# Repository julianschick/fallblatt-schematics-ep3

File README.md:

# Fallblattanzeiger der Deutschen Bahn

Die Deutsche Bahn verwendete lange Zeit standardisierte Fallblattanzeigemodule mit Platinen, die mit *MANTronic* beschriftet sind, also vermutlich von der Firma MAN hergestellt wurden.

Möchte man diese alten Module wieder zum klappern bringen, so hat man grundsätzlich erstmal zwei Möglichkeiten. Die Module wurden offenbar über eine RS485-Schnittstelle angesteuert. Das Protokoll ist vermutlich ein Protokoll ähnlich dem CAN-Bus. Meine gründliche Recherche ergab allerdings keine Quellen im Internet, denen bekannt ist, wie dieses Protokoll genau aussieht. Diese Möglichkeit ist daher eher schwierig.

Eine andere Möglichkeit besteht darin, den zentralen ZiLOG-Microcontroller auf der Platine durch einen eigenen Microcontroller zu ersetzen. Ich habe zu diesem Zweck den ZiLOG-Chip von der Platine geschnitten. Praktischerweise sind auf der Platine nicht nur die SMD-Lötpads für den ZiLOG-Chip, sondern auch etwas größere Pads im DIP-Raster, an die man sehr gut Kabel anlöten kann. Vermutlich ein überbleibsel von älteren Platinenversionen, bei denen ein größerer Microcontroller verwendet wurde.

Mit einer Kombination aus eigener Intuition und Bestätigung durch die Schaltpläne dieses [Hackaday-Projekts](https://hackaday.io/project/9070-fallblattfahrzielanzeige-of-s-bahn-berlin) war es nicht schwer, die Pinbelegung des ZiLOG-Controllers zu ermitteln und so herauszufinden, welche Pins angesteuert bzw. ausgelesen werden müssen. Weiter unten habe ich das mit einer Skizze und einem Foto dokumentiert.

Gemäß der Einteilung im [Wikipedia-Artikel](https://de.wikipedia.org/wiki/Fallblattanzeige) in die vom Aufbau her zu unterscheidenden Epochen 1 bis 4 fällt diese Anzeige in die Epoche 3.

## Funktionsweise

Die Funktionsweise des Fallblattmoduls ist gar nicht so kompliziert. Die Blätter sitzen auf einer Welle die über ein Getriebe von einem Synchronmotor (Berger Lahr RSM 42/12 NG) angetrieben wird, der tatsächlich auch heute noch erhältlich ist ([Datenblatt](https://www.abi.nl/assets/uploads/Downloads/Aandrijvingen/Kleine%20vertragingsmotoren/Synchroonmotoren/Catalogus_RSM_D.pdf)).
Damit der Motor weiß, wann er anhalten soll, sind zwei Infrarot-Transmitter mit Photodioden als Sensoren verbaut. Ein Sensor erzeugt pro fallendem Blatt einen erhöhten Spannungspegel, der andere dient zur Erkennung der Nullposition und weist nur einmal pro Umdrehung der ganzen Welle einen erhöhten Spannungspegel auf. Das ganze wird durch weiße Blenden bewerkstelligt, die beim Vorbeistreichen am Sensor durch die Reflektion der Infrarotstrahlen des Transmitters für mehr Einfall von Infrarotstrahlung in die Photodiode und dadurch einen höheren Spannungspegel sorgen.

Die Verdrahtung der Sensoren auf der Platine ist etwas eigenwillig. Beide Sensoren gehen auf den gleichen Eingang (Sensor IN), an dem mit Hilfe eines ADC die anliegende Spannung messen kann. Um die Sensoren einzeln abfragen zu können, kann man die Sensoren getrennt mit Spannung versorgen (Sensor 1 / Sensor 2) und dann jeweils nur den Sensor auslesen, der mit Spannung versorgt wird. Der Motor ist einfach anzusteuern: Zieht man den Motor-Pin auf LOW, läuft der Motor los, zieht man ihn auf HIGH (3,3V oder 5V), bleibt der Motor stehen.

## Pinbelegung ZiLOG

## Stromversorgung

Die Platine hat zwei Stromkreise, ein Niederspannungsstromkreis für die Steuerungselektronik, der ursprünglich wohl mit 5 V DC betrieben wurde. Ich habe auch mit nur 3.3 V DC keine Probleme festgestellt. Der andere Stromkreis sollte mit etwa 42 V AC bei 50 Hz gespeist werden. Mit diesem Strom wird der Synchronmotor zum Antrieb der Welle betrieben. Die folgende Skizze zeigt die Pinbelegung des Wannensteckers am Rand der Platine bezüglich der Spannungsversorgung.

## Code

Code für die Platine kann in den Repositories [fallblatt-code-legacy](https://github.com/julianschick/fallblatt-code-legacy) und [fallblatt-code](https://github.com/julianschick/fallblatt-code) gefunden werden, wobei letzterer aktueller und mit mehr Funktionen ausgestattet ist.

## Teileliste

Mit passenden Artikelbezeichnungen für den Berliner Elektroteilehändler [Segor](https://www.segor.de).

Anzahl | Beschreibung | Segor-Artikelbezeichnung | Alt. Link
--|--|--|--
1 | Schraubklemme 2-polig RM 7,5mm | *ARK 2-Lift/RM7,5*
1 | Varistor >300V RM 7,5mm | *VDR 300-K 7* | [Reichelt](https://www.reichelt.de/varistor-rm-7-5-mm-300-v-10-epc-b72210-s030-p239932.html)
1 | Brückengleichrichter Rund, Wechselstrompins gegenüber, RM 5mm | *B 80C1500 R* | [Reichelt](https://www.reichelt.de/brueckengleichrichter-100-v-1-5-a-b70c1500rund-p181713.html)
1 | Transformator 9V _Block VB 2,0/1/9_ | | [Reichelt](https://www.reichelt.de/printtrafo-2-va-9-v-222-ma-rm-20-mm-ei-30-15-5-109-p27328.html)
1 | Transformator 2x24V *Block VC 10/2/24* | | [Reichelt](https://www.reichelt.de/printtrafo-10-va-2x-24-v-2x-208-ma-rm-27-5-mm-ei-48-16-8-224-p27492.html)
1 | ESP32-Development-Board (es gibt 2 Varianten bei eBay, für diese Platine wird die unüblichere mit 19 Pins je Reihe und GND/VCC auf gegenüberliegenden, nicht nebeneinanderliegenden Pins benötigt; diese wird oft unter dem Namen _ESP32S_ verkauft.) |
1 | Spannungsregler 3,3V Formfaktor TO-220 _STM LD1117 V33C_ | *LD 1117 V33* | [Reichelt](https://www.reichelt.de/ldo-regler-fest-3-3-v-to-220-ld1117-v33c-p200891.html)
1 | Elektrolytkondensator 470u, >12V, RM 5mm | *ELRA 470u-25/105°lowESR* |
1 | Elektrolytkondensator 10u, >12V, RM 2mm | *ELRA 470u-35/105°* |
1 | Kondensator 100n, >12V, RM 2,5mm | *u10-R2.5-X7R* |
1 | D-Sub Buchse 9-polig, Printmontage 90°, Abstand Pinreihe zu Steckerfläche 10mm | DS09F-90°-10mm |
1 | D-Sub Buchse 25-polig, Printmontage 90°, Abstand Pinreihe zu Steckerfläche 10mm | DS25F-90°-10mm |
4 | Pinheader 20-polig, Female, Vertikal, RM 2,54mm | 
2 | Pinheader 2-polig, Male, Vertikal, RM 2,54mm

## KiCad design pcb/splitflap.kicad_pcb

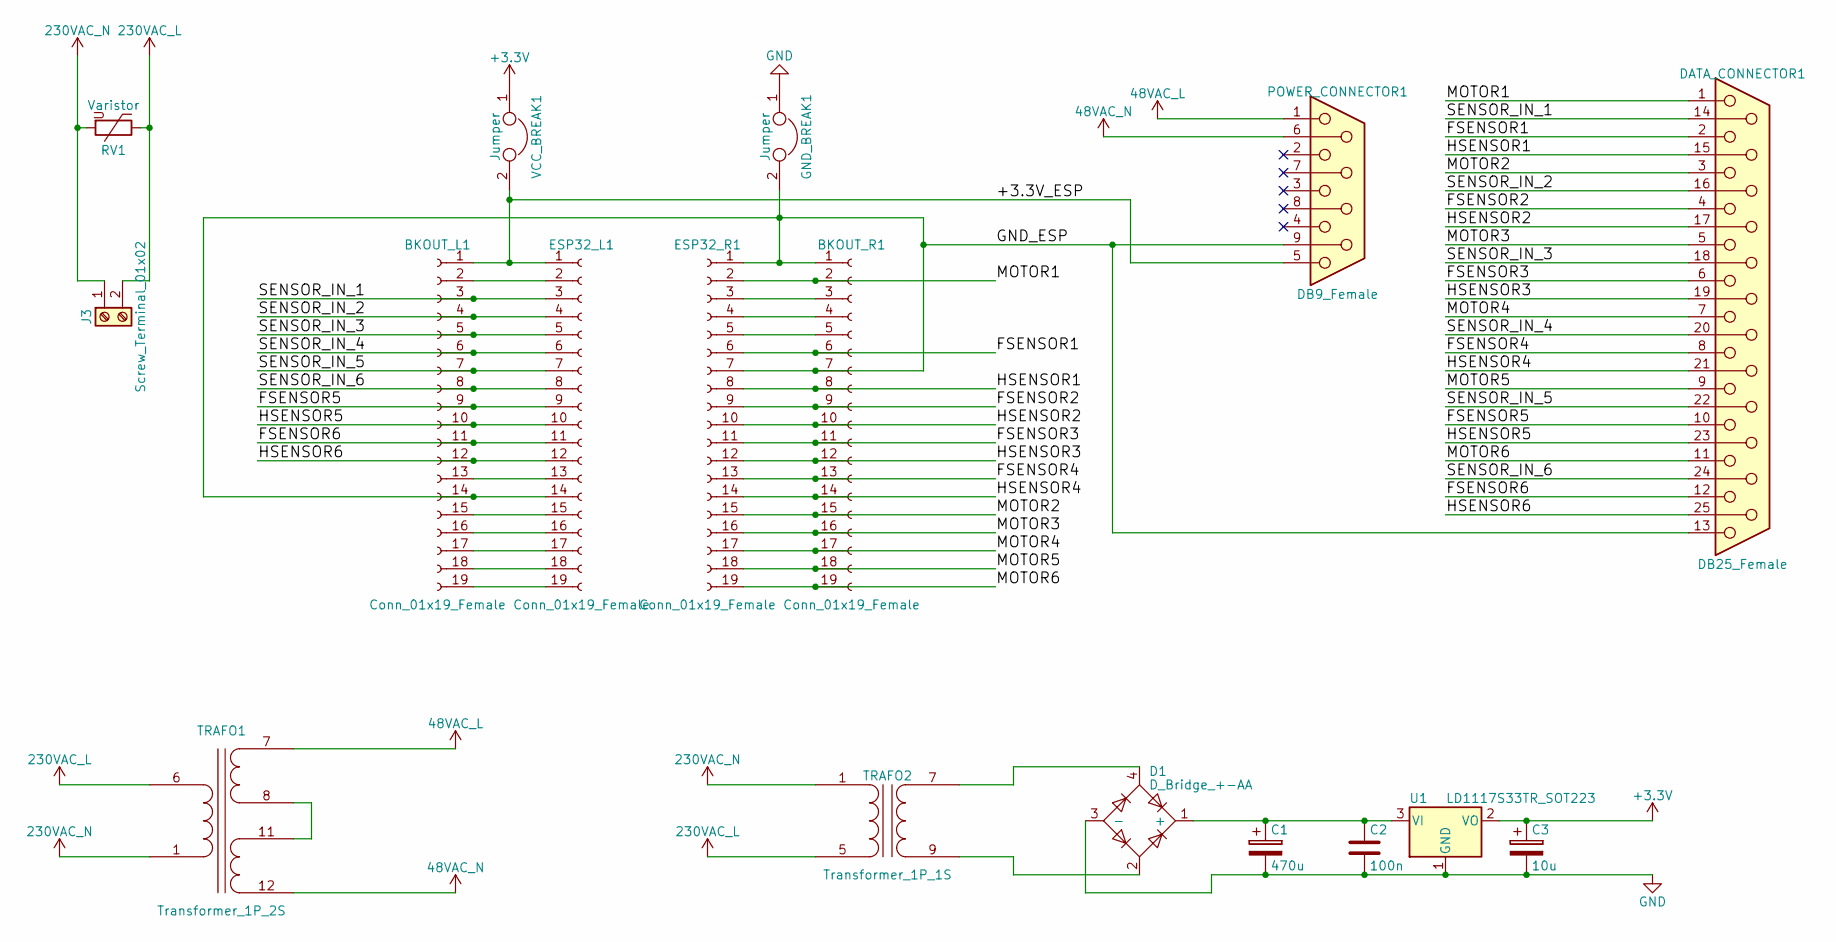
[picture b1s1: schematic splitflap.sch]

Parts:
BKOUT_L1: Conn_01x19_Female; Socket_Strip_Straight_1x20_Pitch2.54mm
BKOUT_R1: Conn_01x19_Female; Socket_Strip_Straight_1x20_Pitch2.54mm
C1: 470u; CP_Radial_D8.0mm_P5.00mm
C2: 100n; C_Rect_L4.0mm_W2.5mm_P2.50mm
C3: 10u; CP_Radial_D4.0mm_P2.00mm
D1: D_Bridge_+-AA; Diode_Bridge_Round_D8.9mm
DATA_CONNECTOR1: DB25_Female; DSUB-25_Female_Horizontal_Pitch2.77x2.54mm_EdgePinOffset9.4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
ESP32_L1, ESP32_R1: Conn_01x19_Female; Socket_Strip_Straight_1x20_Pitch2.54mm
GND_BREAK1: Jumper; Pin_Header_Straight_1x02_Pitch2.54mm
J3: Screw_Terminal_01x02; TerminalBlock_MetzConnect_Type171_RT13702HBWC_Pitch7.50mm
POWER_CONNECTOR1: DB9_Female; DSUB-9_Female_Horizontal_Pitch2.77x2.54mm_EdgePinOffset9.40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
RV1: Varistor; RV_Disc_D12_W3.9_P7.5
TRAFO1: Transformer_1P_2S; Transformer_CHK_EI48-10VA_2xSec_BLOCK
TRAFO2: Transformer_1P_1S; Transformer_CHK_EI30-2VA_1xSec
U1: LD1117S33TR_SOT223; TO-220-3_Vertical
VCC_BREAK1: Jumper; Pin_Header_Straight_1x02_Pitch2.54mm

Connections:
48VAC_L: POWER_CONNECTOR1.1, TRAFO1.7 (SA)
48VAC_N: POWER_CONNECTOR1.6, TRAFO1.12 (SD)
230VAC_L: J3.2, RV1.1, TRAFO1.6 (AA), TRAFO2.5 (AB)
230VAC_N: J3.1, RV1.2, TRAFO1.1 (AB), TRAFO2.1 (AA)
+3V3: C3.1, U1.2 (VO), VCC_BREAK1.1
/+3.3V_ESP: BKOUT_L1.1, ESP32_L1.1, POWER_CONNECTOR1.5, VCC_BREAK1.2
/FSENSOR1: BKOUT_R1.6, DATA_CONNECTOR1.2, ESP32_R1.6
/FSENSOR2: BKOUT_R1.9, DATA_CONNECTOR1.4, ESP32_R1.9
/FSENSOR3: BKOUT_R1.11, DATA_CONNECTOR1.6, ESP32_R1.11
/FSENSOR4: BKOUT_R1.13, DATA_CONNECTOR1.8, ESP32_R1.13
/FSENSOR5: BKOUT_L1.9, DATA_CONNECTOR1.10, ESP32_L1.9
/FSENSOR6: BKOUT_L1.11, DATA_CONNECTOR1.12, ESP32_L1.11
/GND_ESP: BKOUT_L1.14, BKOUT_R1.1, BKOUT_R1.7, DATA_CONNECTOR1.13, ESP32_L1.14, ESP32_R1.1, ESP32_R1.7, GND_BREAK1.2, POWER_CONNECTOR1.9
/HSENSOR1: BKOUT_R1.8, DATA_CONNECTOR1.15, ESP32_R1.8
/HSENSOR2: BKOUT_R1.10, DATA_CONNECTOR1.17, ESP32_R1.10
/HSENSOR3: BKOUT_R1.12, DATA_CONNECTOR1.19, ESP32_R1.12
/HSENSOR4: BKOUT_R1.14, DATA_CONNECTOR1.21, ESP32_R1.14
/HSENSOR5: BKOUT_L1.10, DATA_CONNECTOR1.23, ESP32_L1.10
/HSENSOR6: BKOUT_L1.12, DATA_CONNECTOR1.25, ESP32_L1.12
/MOTOR1: BKOUT_R1.2, DATA_CONNECTOR1.1, ESP32_R1.2
/MOTOR2: BKOUT_R1.15, DATA_CONNECTOR1.3, ESP32_R1.15
/MOTOR3: BKOUT_R1.16, DATA_CONNECTOR1.5, ESP32_R1.16
/MOTOR4: BKOUT_R1.17, DATA_CONNECTOR1.7, ESP32_R1.17
/MOTOR5: BKOUT_R1.18, DATA_CONNECTOR1.9, ESP32_R1.18
/MOTOR6: BKOUT_R1.19, DATA_CONNECTOR1.11, ESP32_R1.19
/SENSOR_IN_1: BKOUT_L1.3, DATA_CONNECTOR1.14, ESP32_L1.3
/SENSOR_IN_2: BKOUT_L1.4, DATA_CONNECTOR1.16, ESP32_L1.4
/SENSOR_IN_3: BKOUT_L1.5, DATA_CONNECTOR1.18, ESP32_L1.5
/SENSOR_IN_4: BKOUT_L1.6, DATA_CONNECTOR1.20, ESP32_L1.6
/SENSOR_IN_5: BKOUT_L1.7, DATA_CONNECTOR1.22, ESP32_L1.7
/SENSOR_IN_6: BKOUT_L1.8, DATA_CONNECTOR1.24, ESP32_L1.8
GND: C1.2, C2.2, C3.2, D1.3 (-), GND_BREAK1.1, U1.1 (GND)
unnamed: BKOUT_L1.2, ESP32_L1.2
unnamed: BKOUT_L1.13, ESP32_L1.13
unnamed: BKOUT_L1.15, ESP32_L1.15
unnamed: BKOUT_L1.16, ESP32_L1.16
unnamed: BKOUT_L1.17, ESP32_L1.17
unnamed: BKOUT_L1.18, ESP32_L1.18
unnamed: BKOUT_L1.19, ESP32_L1.19
unnamed: BKOUT_R1.3, ESP32_R1.3
unnamed: BKOUT_R1.4, ESP32_R1.4
unnamed: BKOUT_R1.5, ESP32_R1.5
unnamed: C1.1, C2.1, D1.1 (+), U1.3 (VI)
unnamed: D1.2, TRAFO2.9 (SA)
unnamed: D1.4, TRAFO2.7 (SB)
unnamed: TRAFO1.8 (SB), TRAFO1.11 (SC)

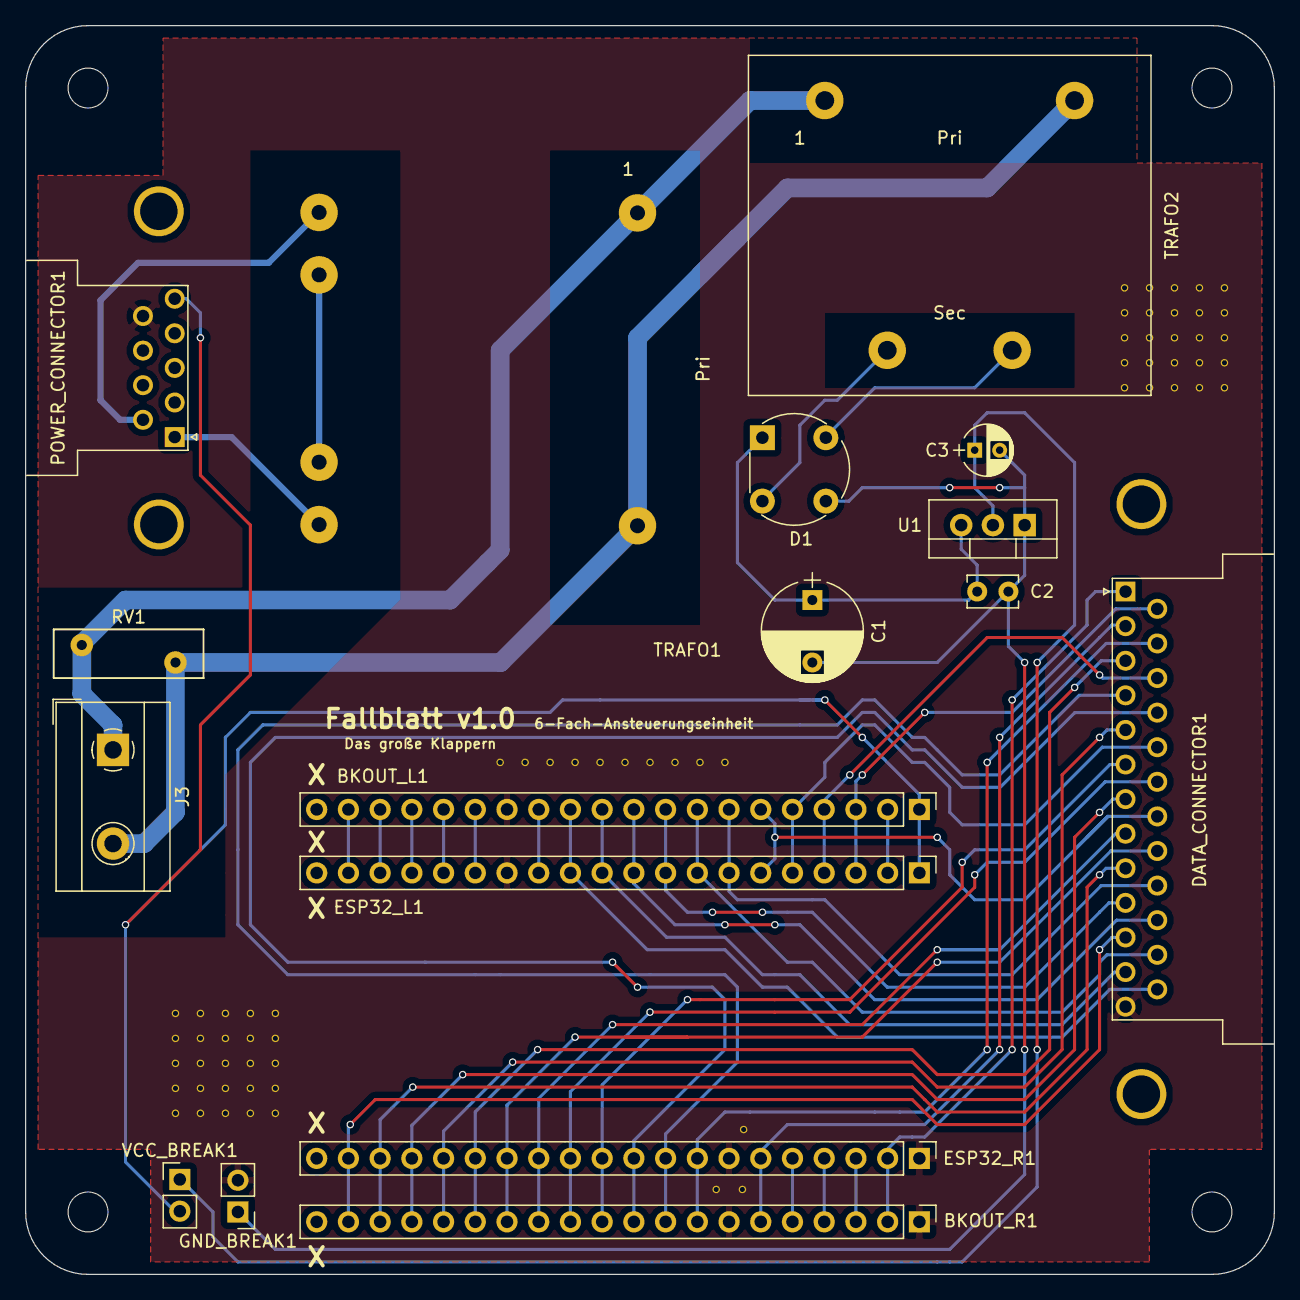
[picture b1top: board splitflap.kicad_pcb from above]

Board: 2 copper layers, 100.0 x 100.0 mm, 17 parts (0 on the bottom side), 46 nets.

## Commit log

2018-03-22 initial data input
2018-03-23 http server
2018-03-25 modularization
2018-03-26 images added
2018-03-26 update schaltskizze
2018-03-26 update schaltskizze 2
2018-03-26 httpclient
2018-03-26 http client and nvs
2018-03-27 nvs module / http pull
2018-03-30 platine v1
2018-03-31 100x100-platine
2018-04-12 footprints
2018-04-16 wiring
2018-04-16 powerground
2018-04-16 fix vias
2018-04-16 net width trafo1 wrong
2018-04-19 labels
2018-04-19 small bugfixes in microcontroller code
2018-04-19 gerber files
2018-05-09 bugfixes / extension bt interface
2018-05-14 getip
2018-05-16 bugfixes / getip
2019-01-22 special symbols moved
2019-10-24 moved code away
2019-10-24 add license
